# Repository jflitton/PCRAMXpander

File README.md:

# PCRAMXpander

> **Note:** This project is currently untested. The first batch of boards has been ordered for testing.

An 8MB memory expansion card for the 16-bit ISA bus, designed as a modern alternative to the somewhat difficult to find ISA version of [IBM's Memory Expansion boards](https://www.ardent-tool.com/memory/IBM_Expansion.html#1_8MB).

This card should likely only be used in systems where the ISA bus is clocked at the same rate as the processor (often the case for 286-based systems).  While this board should work on faster 386 and 486-based systems, this board's memory will significantly underperform the motherboard-attached memory.

## Features

- **8MB total memory** using two 4MB SRAM chips (AS6C3216A)
- **Configurable base address** supporting systems with 1MB, 2MB, 4MB, or 8MB of existing memory
- **Zero wait state mode** for faster memory access on supported systems
- **Simple design** with address decoding handled by a single GAL (ATF16V8B)

## Configuration

### Memory Jumpers (JP1, JP2)

Configure the board's starting address based on your system's existing memory:

| Existing Memory | JP1    | JP2    | Memory Range      |
|-----------------|--------|--------|-------------------|
| 1MB             | Closed | Closed | 1MB – 9MB         |
| 2MB             | Open   | Closed | 2MB – 10MB        |
| 4MB             | Closed | Open   | 4MB – 12MB        |
| 8MB             | Open   | Open   | 8MB – 16MB        |

> **Note:** Configurations with less than 1MB of existing memory are not currently supported.

### Zero Wait State Jumper (JP3)

Installing a jumper on JP3 enables zero wait state mode. This is **recommended** for systems that support it, as it significantly improves memory access performance.

## Theory of Operation

### Overview

The PCRAMXpander provides 8MB of additional memory to an ISA-bus system using two 4MB SRAM chips. A GAL (U1) handles address decoding, while buffer ICs manage the data and address buses.

### Address Decoding (U1 – ATF16V8B)

The GAL monitors the upper address lines (LA23–LA20) to determine which 1MB block is being accessed. Based on the jumper configuration (JP1, JP2), it calculates whether the requested address falls within the board's memory range.

The memory is split into two 4MB banks:
- **Low bank (U5):** First 4MB of the expansion range
- **High bank (U6):** Second 4MB of the expansion range

The GAL generates active-low chip select signals (`CS_LO`, `CS_HI`) for each bank. It also asserts:
- **MEMCS16:** Indicates 16-bit memory is present at this address
- **NOWS:** Signals zero wait state capability (directly from JP3 setting)

Both MEMCS16 and NOWS are active-low, open-collector outputs, allowing multiple ISA cards to share these signals.

### Bus Interface

| IC  | Function |
|-----|----------|
| U2 (SN74LVCR16245ADGGR) | Bidirectional 16-bit data buffer between ISA bus and SRAM |
| U3 (SN74LVC16244ADGGR) | 16-bit address buffer (A1–A16) |
| U4 (SN74LVC16244A) | Additional address buffering |
| U7 (SN74LVC573APWR) | Address latch for upper address bits |

The data buffer (U2) is enabled by the `TRANS_EN` signal from the GAL whenever either SRAM chip is selected. Its direction is controlled by the ISA bus read/write signals.

### Power Supply

A 3.3V LDO regulator (VR1 – LDL1117S33R) provides power to the low-voltage SRAM and buffer ICs from the ISA bus 5V rail. Bypass capacitors ensure stable operation.

### Timing

When zero wait state mode is enabled (JP3 closed), the board signals to the host that no additional wait states are required for memory access. The AS6C3216A SRAM has a 55ns access time, which is fast enough for zero wait state operation on most ISA systems.

## License

This work is licensed under the [Creative Commons NonCommercial 4.0 International license](https://creativecommons.org/licenses/by-nc/4.0/).

## Authors

- [Jeff Flitton](mailto:jeff@flitton.dev) – Project creator

## Disclaimer

This project is provided as-is, without any express or implied warranty. By using, building, or modifying this hardware, you acknowledge that you do so at your own risk. The authors and contributors are not responsible for any damage, data loss, injury, or other consequences resulting from its use.

This project is a community-driven, open-hardware design intended for educational and hobbyist use. It is not affiliated with, endorsed by, or supported by IBM or any successor entities.

All trademarks are the property of their respective owners and are used here for descriptive and compatibility purposes only.

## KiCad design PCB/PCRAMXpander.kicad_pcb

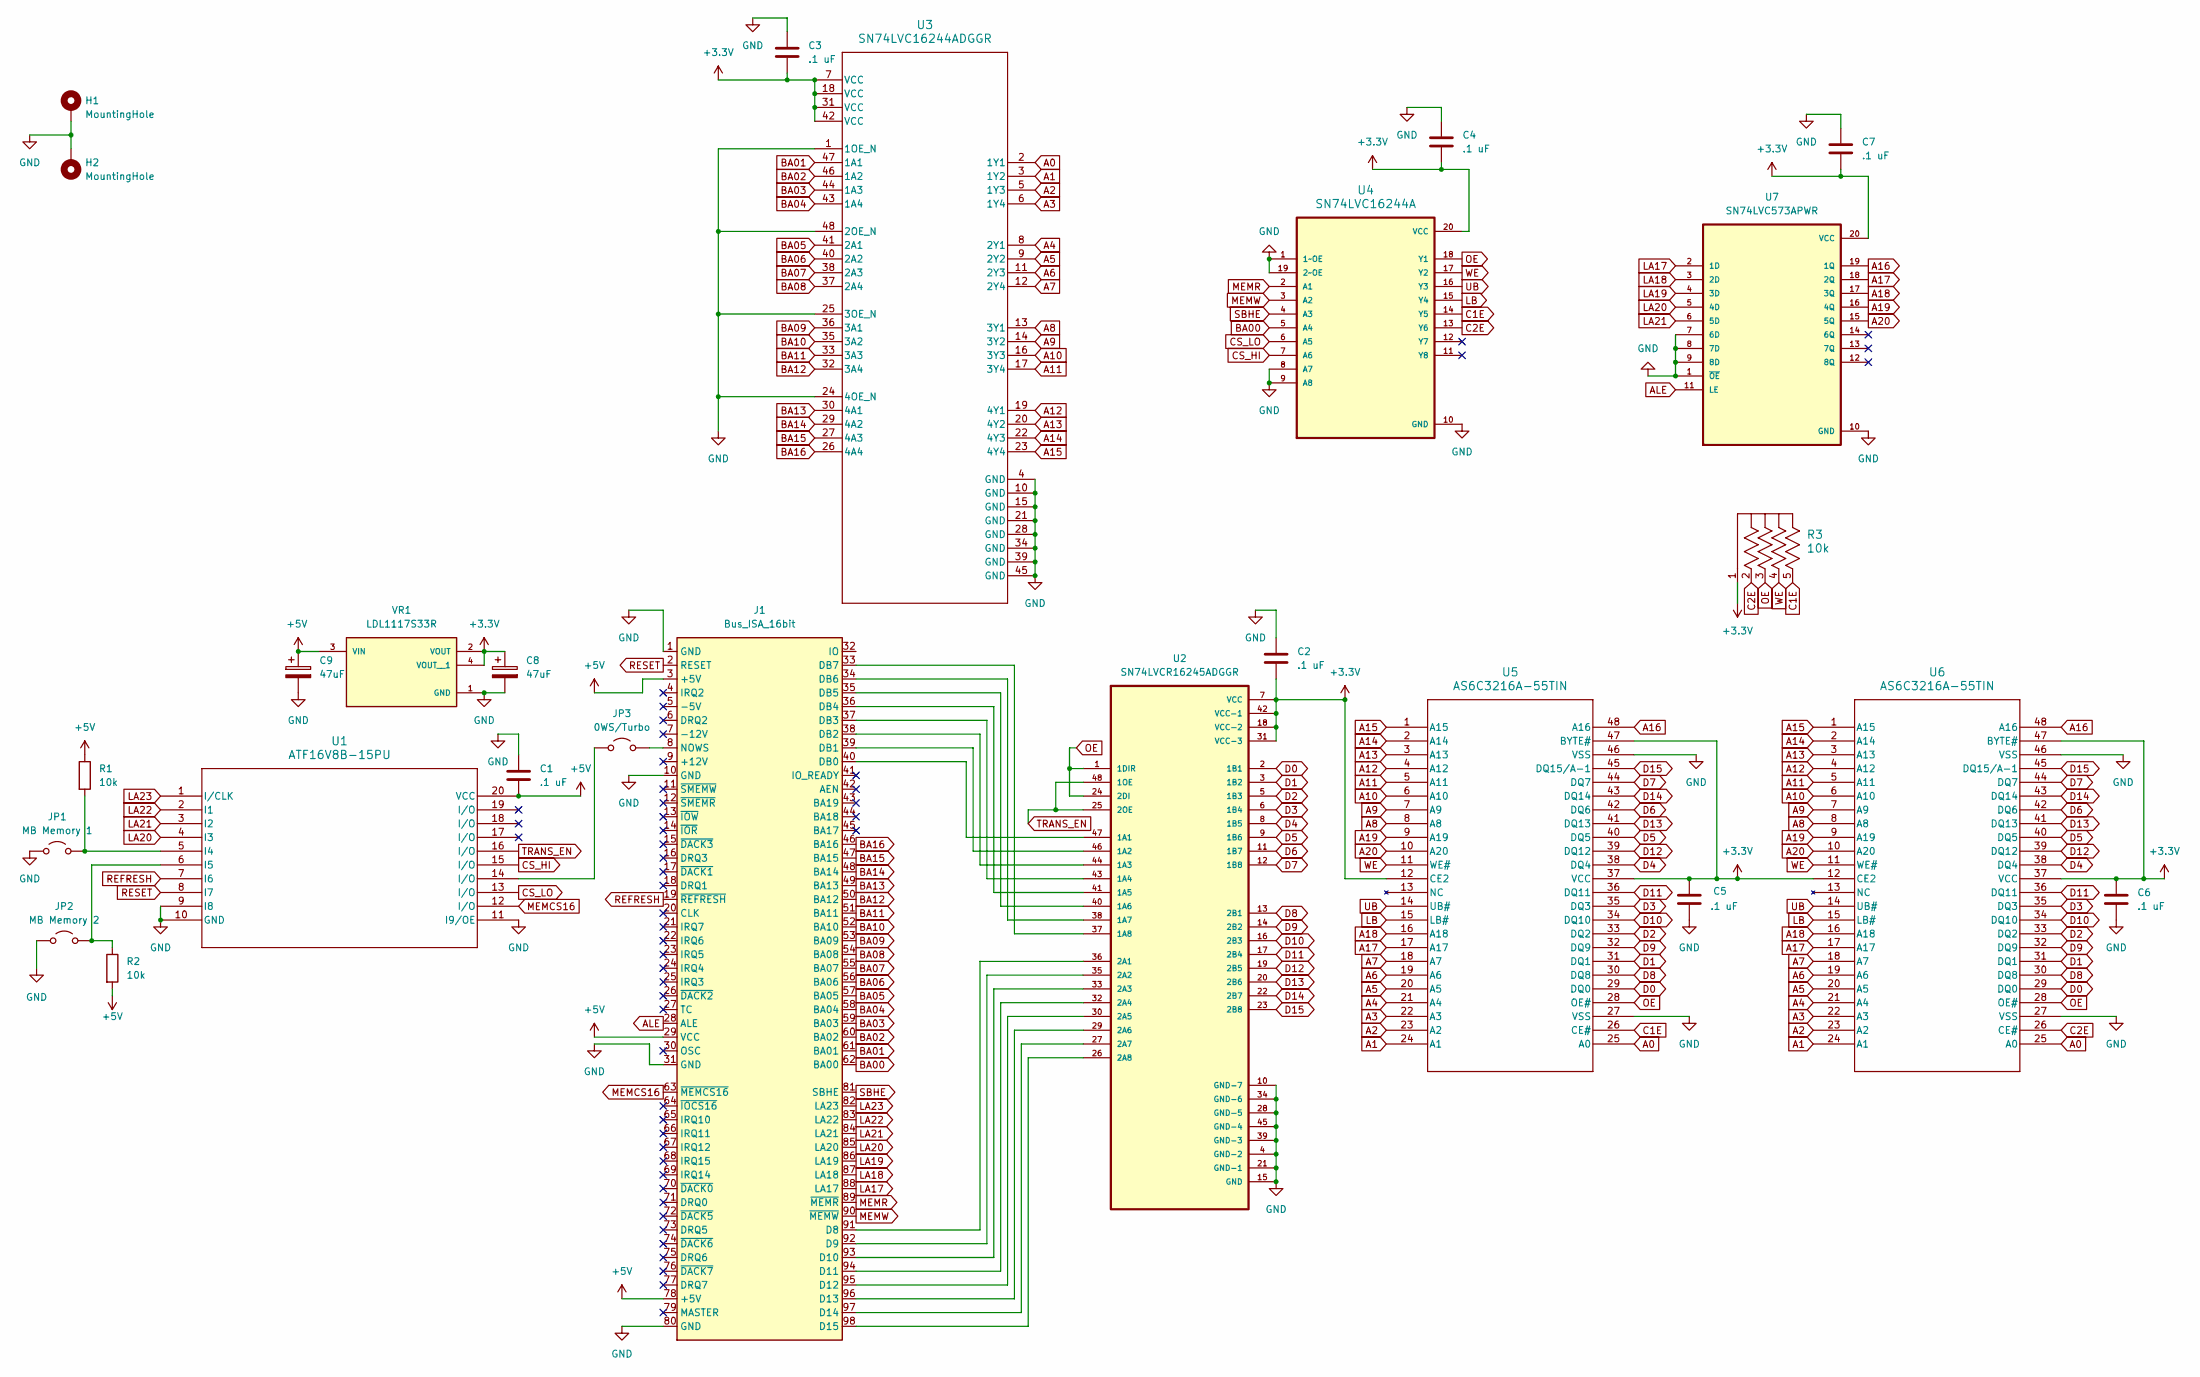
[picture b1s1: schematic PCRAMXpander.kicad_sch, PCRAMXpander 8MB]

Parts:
C1, C2, C3, C4, C5, C6, C7: .1 uF; C_0805_2012Metric_Pad1.18x1.45mm_HandSolder
C8, C9: 47uF; CAP_PAN_5X11_PAN
H1, H2: MountingHole; MountingHole_3.2mm_M3_Pad_Via
J1: Bus_ISA_16bit; BUS_AT
JP1: MB Memory 1; PinHeader_1x02_P2.54mm_Vertical
JP2: MB Memory 2; PinHeader_1x02_P2.54mm_Vertical
JP3: 0WS/Turbo; PinHeader_1x02_P2.54mm_Vertical
R1, R2: 10k; R_0805_2012Metric_Pad1.20x1.40mm_HandSolder
R3: 10k; CSC05_VIS
U1: ATF16V8B-15PU; 20P3_ATM
U2: SN74LVCR16245ADGGR; SOP50P810X120-48N
U3: SN74LVC16244ADGGR; DGG0048A_N
U4: SN74LVC16244A; SOP65P640X120-20N
U5, U6: AS6C3216A-55TIN; TSOP-I-48_12X20_ALL
U7: SN74LVC573APWR; SOP65P640X120-20N
VR1: LDL1117S33R; SOT230P700X180-4N; PARTREV 7

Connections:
+3.3V: C2.2, C3.2, C4.2, C5.1, C6.1, C7.2, C8.1, R3.1, U2.7 (VCC), U2.18 (VCC-2), U2.31 (VCC-3), U2.42 (VCC-1), U3.7 (VCC), U3.18 (VCC), U3.31 (VCC), U3.42 (VCC), U4.20 (VCC), U5.12 (CE2), U5.37 (VCC), U5.47 (BYTE#), U6.12 (CE2), U6.37 (VCC), U6.47 (BYTE#), U7.20 (VCC), VR1.2 (VOUT), VR1.4 (VOUT__1)
+5V: C1.2, C9.1, J1.3 (+5V), J1.29 (VCC), J1.78 (+5V), R1.1, R2.2, U1.20 (VCC), VR1.3 (VIN)
A0: U3.2 (1Y1), U5.25 (A0), U6.25 (A0)
A1: U3.3 (1Y2), U5.24 (A1), U6.24 (A1)
A2: U3.5 (1Y3), U5.23 (A2), U6.23 (A2)
A3: U3.6 (1Y4), U5.22 (A3), U6.22 (A3)
A4: U3.8 (2Y1), U5.21 (A4), U6.21 (A4)
A5: U3.9 (2Y2), U5.20 (A5), U6.20 (A5)
A6: U3.11 (2Y3), U5.19 (A6), U6.19 (A6)
A7: U3.12 (2Y4), U5.18 (A7), U6.18 (A7)
A8: U3.13 (3Y1), U5.8 (A8), U6.8 (A8)
A9: U3.14 (3Y2), U5.7 (A9), U6.7 (A9)
A10: U3.16 (3Y3), U5.6 (A10), U6.6 (A10)
A11: U3.17 (3Y4), U5.5 (A11), U6.5 (A11)
A12: U3.19 (4Y1), U5.4 (A12), U6.4 (A12)
A13: U3.20 (4Y2), U5.3 (A13), U6.3 (A13)
A14: U3.22 (4Y3), U5.2 (A14), U6.2 (A14)
A15: U3.23 (4Y4), U5.1 (A15), U6.1 (A15)
A16: U5.48 (A16), U6.48 (A16), U7.19 (1Q)
A17: U5.17 (A17), U6.17 (A17), U7.18 (2Q)
A18: U5.16 (A18), U6.16 (A18), U7.17 (3Q)
A19: U5.9 (A19), U6.9 (A19), U7.16 (4Q)
A20: U5.10 (A20), U6.10 (A20), U7.15 (5Q)
ALE: J1.28 (ALE), U7.11 (LE)
BA00: J1.62 (BA00), U4.5 (A4)
BA01: J1.61 (BA01), U3.47 (1A1)
BA02: J1.60 (BA02), U3.46 (1A2)
BA03: J1.59 (BA03), U3.44 (1A3)
BA04: J1.58 (BA04), U3.43 (1A4)
BA05: J1.57 (BA05), U3.41 (2A1)
BA06: J1.56 (BA06), U3.40 (2A2)
BA07: J1.55 (BA07), U3.38 (2A3)
BA08: J1.54 (BA08), U3.37 (2A4)
BA09: J1.53 (BA09), U3.36 (3A1)
BA10: J1.52 (BA10), U3.35 (3A2)
BA11: J1.51 (BA11), U3.33 (3A3)
BA12: J1.50 (BA12), U3.32 (3A4)
BA13: J1.49 (BA13), U3.30 (4A1)
BA14: J1.48 (BA14), U3.29 (4A2)
BA15: J1.47 (BA15), U3.27 (4A3)
BA16: J1.46 (BA16), U3.26 (4A4)
C1E: R3.5, U4.14 (Y5), U5.26 (CE#)
C2E: R3.2, U4.13 (Y6), U6.26 (CE#)
CS_HI: U1.15 (I/O), U4.7 (A6)
CS_LO: U1.13 (I/O), U4.6 (A5)
D0: U2.2 (1B1), U5.29 (DQ0), U6.29 (DQ0)
D1: U2.3 (1B2), U5.31 (DQ1), U6.31 (DQ1)
D2: U2.5 (1B3), U5.33 (DQ2), U6.33 (DQ2)
D3: U2.6 (1B4), U5.35 (DQ3), U6.35 (DQ3)
D4: U2.8 (1B5), U5.38 (DQ4), U6.38 (DQ4)
D5: U2.9 (1B6), U5.40 (DQ5), U6.40 (DQ5)
D6: U2.11 (1B7), U5.42 (DQ6), U6.42 (DQ6)
D7: U2.12 (1B8), U5.44 (DQ7), U6.44 (DQ7)
D8: U2.13 (2B1), U5.30 (DQ8), U6.30 (DQ8)
D9: U2.14 (2B2), U5.32 (DQ9), U6.32 (DQ9)
D10: U2.16 (2B3), U5.34 (DQ10), U6.34 (DQ10)
D11: U2.17 (2B4), U5.36 (DQ11), U6.36 (DQ11)
D12: U2.19 (2B5), U5.39 (DQ12), U6.39 (DQ12)
D13: U2.20 (2B6), U5.41 (DQ13), U6.41 (DQ13)
D14: U2.22 (2B7), U5.43 (DQ14), U6.43 (DQ14)
D15: U2.23 (2B8), U5.45 (DQ15/A-1), U6.45 (DQ15/A-1)
GND: C1.1, C2.1, C3.1, C4.1, C5.2, C6.2, C7.1, C8.2, C9.2, H1.1, H2.1, J1.1 (GND), J1.10 (GND), J1.31 (GND), J1.80 (GND), JP1.1 (A), JP2.1 (A), U1.9 (I8), U1.10 (GND), U1.11 (I9/OE), U2.4 (GND-2), U2.10 (GND-7), U2.15 (GND), U2.21 (GND-1), U2.28 (GND-5), U2.34 (GND-6), U2.39 (GND-3), U2.45 (GND-4), U3.1 (1OE_N), U3.4 (GND), U3.10 (GND), U3.15 (GND), U3.21 (GND), U3.24 (4OE_N), U3.25 (3OE_N), U3.28 (GND), U3.34 (GND), U3.39 (GND), U3.45 (GND), U3.48 (2OE_N), U4.1 (1~OE), U4.8 (A7), U4.9 (A8), U4.10 (GND), U4.19 (2~OE), U5.27 (VSS), U5.46 (VSS), U6.27 (VSS), U6.46 (VSS), U7.1 (~OE), U7.7 (6D), U7.8 (7D), U7.9 (8D), U7.10 (GND), VR1.1 (GND)
LA17: J1.88 (LA17), U7.2 (1D)
LA18: J1.87 (LA18), U7.3 (2D)
LA19: J1.86 (LA19), U7.4 (3D)
LA20: J1.85 (LA20), U1.4 (I3), U7.5 (4D)
LA21: J1.84 (LA21), U1.3 (I2), U7.6 (5D)
LA22: J1.83 (LA22), U1.2 (I1)
LA23: J1.82 (LA23), U1.1 (I/CLK)
LB: U4.15 (Y4), U5.15 (LB#), U6.15 (LB#)
MEMCS16: J1.63 (~MEMCS16), U1.12 (I/O)
MEMR: J1.89 (~MEMR), U4.2 (A1)
MEMW: J1.90 (~MEMW), U4.3 (A2)
unnamed: J1.91 (D8), U2.36 (2A1)
unnamed: J1.92 (D9), U2.35 (2A2)
unnamed: J1.93 (D10), U2.33 (2A3)
unnamed: J1.94 (D11), U2.32 (2A4)
unnamed: J1.95 (D12), U2.30 (2A5)
unnamed: J1.96 (D13), U2.29 (2A6)
unnamed: J1.97 (D14), U2.27 (2A7)
unnamed: J1.98 (D15), U2.26 (2A8)
unnamed: J1.40 (DB0), U2.47 (1A1)
unnamed: J1.39 (DB1), U2.46 (1A2)
unnamed: J1.38 (DB2), U2.44 (1A3)
unnamed: J1.37 (DB3), U2.43 (1A4)
unnamed: J1.36 (DB4), U2.41 (1A5)
unnamed: J1.35 (DB5), U2.40 (1A6)
unnamed: J1.34 (DB6), U2.38 (1A7)
unnamed: J1.33 (DB7), U2.37 (1A8)
unnamed: J1.8 (NOWS), JP3.2 (B)
unnamed: JP1.2 (B), R1.2, U1.5 (I4)
unnamed: JP2.2 (B), R2.1, U1.6 (I5)
unnamed: JP3.1 (A), U1.14 (I/O)
OE: R3.3, U2.1 (1DIR), U2.24 (2DI), U4.18 (Y1), U5.28 (OE#), U6.28 (OE#)
REFRESH: J1.19 (~REFRESH), U1.7 (I6)
RESET: J1.2 (RESET), U1.8 (I7)
SBHE: J1.81 (SBHE), U4.4 (A3)
TRANS_EN: U1.16 (I/O), U2.25 (2OE), U2.48 (1OE)
UB: U4.16 (Y3), U5.14 (UB#), U6.14 (UB#)
WE: R3.4, U4.17 (Y2), U5.11 (WE#), U6.11 (WE#)

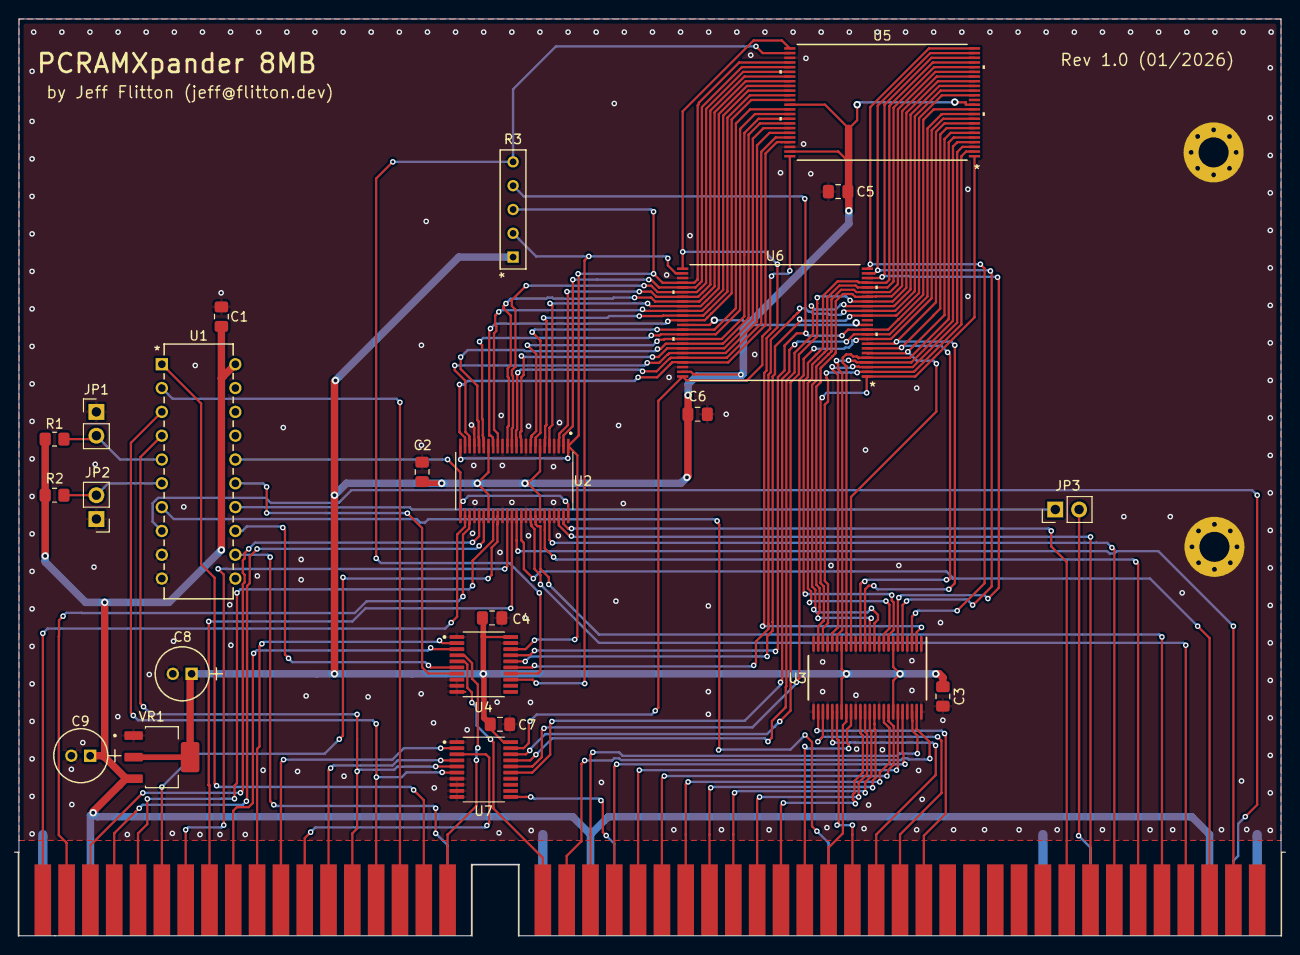
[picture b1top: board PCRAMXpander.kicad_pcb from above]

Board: 2 copper layers, 134.6 x 97.8 mm, 26 parts (0 on the bottom side), 100 nets.

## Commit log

2026-01-01 Symbol libraries
2026-01-01 Switching to 245 w/ built-in resistors
2026-01-01 Initial draft of GAL code
2026-01-02 Routing has begun
2026-01-03 Playing with routing a bit more
2026-01-03 Power routing only
2026-01-03 Potentially improved chip orientation
2026-01-03 manual routing of U3 right side
2026-01-03 More manual routing
2026-01-03 Moving U3 for more routing space
2026-01-04 Ram wired up
2026-01-04 5V done
2026-01-04 5v refinement
2026-01-04 SIP5 resistor pack
2026-01-04 Power refinement, ISA fingers
2026-01-04 Power refinement
2026-01-04 U6 routing
2026-01-05 Memory chips routed
2026-01-05 Low data lines routed
2026-01-05 GAL and U4 routes
2026-01-05 All traces routed
2026-01-06 DRC clear
2026-01-11 Transparent latch for high address lines
2026-01-11 Revert "More manual routing"
    This reverts commit 0982fc74f345ec59384cba768510721dd6743d85.
2026-01-11 Revert "More manual routing"
    This reverts commit 1ef752c8dd37f4f521128f7022dea4d2c55a3ae6.
2026-01-11 Revert "More manual routing"
    This reverts commit 8fc89334eef3b822060e9ccc43876c88ada5381e.
2026-01-11 Revert "More manual routing"
    This reverts commit 4701405ffdf181303b86cdb3b1250737cb80df36.
2026-01-11 Revert "More manual routing"
    This reverts commit 8a1b72b23a01502d9d5028c2d37e0cfdb243fa78.
2026-01-11 Revert "More manual routing"
    This reverts commit 646e4b39c57eedcae7559b9f3577459cb52bf620.
2026-01-11 Revert "More manual routing"
    This reverts commit eb176bf1cf606b5faa7e563e33fd253a07104509.
2026-01-11 Revert "More manual routing"
    This reverts commit ad645bdee1b61d8c4c4095e91a6cf0d337db442c.
2026-01-11 Revert "More manual routing"
    This reverts commit b921debae46f28068d9de22bc133656cc87b6f20.
2026-01-11 Revert "More manual routing"
    This reverts commit 47449c23b7240c85fd4465f78316c60ac3030f38.
2026-01-11 Silkscreen updates, reset line wired
2026-01-11 Adding BOM, a little trace cleanup
2026-01-11 Added mounting holes
2026-01-11 Moving some labels
2026-01-12 First readme
2026-01-12 Updating readme
2026-01-12 Fixing BOM
2026-01-12 Adding rendered card image
2026-01-29 Fixing value
2026-01-29 Updating credits in PLD
2026-01-29 PLD updates
